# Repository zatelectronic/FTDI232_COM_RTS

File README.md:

<div align="center">

# FTDI232 COM RTS

**Conversor USB-Serial compacto com conector USB-C, chip FT232RL, seleção de tensão 3,3V / 5V, 3 LEDs de status e saída com pino RTS — totalmente SMD**

</div>

---

## 📋 Índice

- [FTDI232 COM RTS](#ftdi232-com-rts)
  - [📋 Índice](#-índice)
  - [Visão Geral](#visão-geral)
  - [Renders 3D](#renders-3d)
  - [Funcionalidades](#funcionalidades)
  - [Diagrama de Blocos](#diagrama-de-blocos)
  - [Especificações Técnicas](#especificações-técnicas)
  - [Lista de Materiais](#lista-de-materiais)
  - [Pinagem dos Conectores](#pinagem-dos-conectores)
    - [J2 — Saída Serial (6 pinos angulado)](#j2--saída-serial-6-pinos-angulado)
    - [JP1 — Seleção de Tensão](#jp1--seleção-de-tensão)
  - [Seleção de Tensão — JP1](#seleção-de-tensão--jp1)
  - [Aplicações](#aplicações)
  - [Estrutura do Repositório](#estrutura-do-repositório)
  - [Como Usar](#como-usar)
    - [Conexão com Arduino (programação)](#conexão-com-arduino-programação)
    - [Conexão com ESP8266 / ESP32](#conexão-com-esp8266--esp32)
    - [Instalação de drivers](#instalação-de-drivers)
  - [Sobre](#sobre)

---

## Visão Geral

**FTDI232 COM RTS** é um módulo conversor **USB para Serial (UART)** compacto e totalmente SMD, projetado pela **ZAT ELECTRONIC** utilizando **KiCad 10**. O módulo é baseado no chip **FT232RL** (SSOP-28), reconhecido automaticamente pelo sistema operacional sem necessidade de drivers adicionais na maioria das plataformas.

O diferencial deste módulo em relação a conversores convencionais é a presença do **pino RTS** no conector de saída de 6 pinos, além do tradicional conjunto **GND / VCC / TX / RX / DTR**. A tensão de saída é selecionável entre **3,3V e 5V** via jumper **(JP1)**, tornando o módulo compatível com uma ampla variedade de microcontroladores e módulos seriais. A entrada USB utiliza o conector **USB-C** (USB4105GFA SMD).

> 💡 Ideal para programação de Arduino bootloader, ESP8266, ESP32 sem USB nativo, módulos GSM, GPS e qualquer dispositivo com interface UART.

---

## Renders 3D

<div align="center">

*Vista superior — FT232RL SSOP-28, USB-C, LEDs SMD 0805, jumper JP1 e conector de 6 pinos (render da versão original)*

<br/>

*Vista isométrica — layout compacto SMD com saída de 6 pinos angulada*

</div>

---

## Funcionalidades

- ✅ **Chip FT232RL** (SSOP-28 SMD) — conversor USB-Serial com oscilador e EEPROM internos
- ✅ **Conector USB-C** (USB4105GFA) — USB 2.0, resistores de 5,1 kΩ no CC1/CC2 (R1, R2)
- ✅ **Seleção de tensão 5V / 3,3V** via jumper JP1 — define o pino VCC do J2 **e o VCCIO do FT232RL** (nível lógico das saídas)
- ✅ **Pino RTS** disponível no conector de saída
- ✅ **Pino DTR** disponível — reset automático de Arduino e bootloaders
- ✅ **3 LEDs SMD 0805** — D2 alimentação, D3 TX (CBUS0), D4 RX (CBUS1)
- ✅ **Diodo Schottky SS1P3L** (D1, DO-220AA SMD) — proteção contra corrente reversa entre VBUS e +5V
- ✅ **Capacitor de tântalo 10µF/16V** (C2, EIA-3216 SMD) + 100nF (C1) — filtragem da entrada VBUS
- ✅ **Desacoplamento do FT232RL** — 100nF no VCC (C3) e 1µF no 3V3OUT (C4), 0805 SMD
- ✅ **Resistores 1206 SMD** — R1/R2 5,1 kΩ (CC), R3 0 Ω (VBUS), R4–R6 1 kΩ (LEDs)
- ✅ **Saída por barra de 6 pinos 90°** (J2) na borda da placa

---

## Diagrama de Blocos

```
┌─────────────┐       ┌──────────────────┐       ┌─────────────────────────┐
│  USB-C  J1  │       │   FT232RL  U1    │       │  J2 (6 pinos 90°)       │
│ USB4105GFA  │──────►│   SSOP-28        │──────►│  1 DTR                  │
│  D+ / D-    │  USB  │  TXD/RXD/DTR/RTS │       │  2 RXD (entrada)        │
└──────┬──────┘       │  CBUS0 / CBUS1   │       │  3 TXD (saída)          │
       │ VBUS         │  VCCIO ◄── VOUT  │       │  4 VCC = VOUT           │
   R3 0Ω → D1 SS1P3L  └──────────────────┘       │  5 RTS                  │
       → +5V (VCC)            │ 3V3OUT           │  6 GND                  │
                          [JP1] 1-2 = 5V  /  2-3 = 3,3V → VOUT
                                                 └─────────────────────────┘
   D2 PWR (+5V)    D3 TX (CBUS0)    D4 RX (CBUS1)
```

---

## Especificações Técnicas

| Parâmetro | Valor |
|-----------|-------|
| **Chip conversor** | FT232RL (SSOP-28 SMD) |
| **Conector USB** | USB-C — USB4105GFA (USB 2.0) |
| **Tensão de saída / nível lógico** | 5V ou 3,3V (JP1 → VOUT = VCC do J2 e VCCIO do FT232RL) |
| **Saída 3,3V** | regulador interno do FT232RL (3V3OUT) — até ~50 mA |
| **Pinos do J2** | DTR, RXD, TXD, VCC, RTS, GND |
| **LEDs de status** | 3x SMD 0805 — D2 PWR, D3 TX, D4 RX |
| **Diodo de proteção** | SS1P3L — Schottky (DO-220AA SMD) |
| **Capacitor de entrada** | 10µF / 16V tântalo (EIA-3216) + 100nF |
| **Capacitores do FT232RL** | 100nF (VCC) e 1µF (3V3OUT), 0805 SMD |
| **Resistores** | 0Ω, 1kΩ, 5,1kΩ (1206 SMD) |
| **Jumper de tensão** | JP1 — 3 pinos 2,54mm (header vertical) |
| **Conector de saída** | J2 — 6 pinos 90° 2,54mm na borda |
| **Placa** | 41,7 × 18,4 mm, 2 camadas |
| **Ferramenta de Projeto** | KiCad 10 |

---

## Lista de Materiais

| Ref | Componente | Valor / Parte | Encapsulamento |
|-----|-----------|--------------|----------------|
| U1 | Conversor USB-Serial | FT232RL | SSOP-28 SMD |
| J1 | Conector USB | USB-C (USB4105GFA) | SMD + furos de fixação |
| J2 | Conector de Saída | 6 pinos — DTR/RXD/TXD/VCC/RTS/GND | Barra 90° 2,54mm |
| JP1 | Jumper de Tensão | 5V / VOUT / 3,3V | Header 3 pinos 2,54mm |
| D1 | Diodo Schottky | SS1P3L | DO-220AA (SMP) |
| D2 | LED PWR | LED 0805 | 0805 |
| D3 | LED TX | LED 0805 | 0805 |
| D4 | LED RX | LED 0805 | 0805 |
| C1 | Capacitor cerâmico (VBUS) | 100nF | 0805 SMD |
| C2 | Capacitor de tântalo (VBUS) | 10µF / 16V | EIA-3216-18 (A) |
| C3 | Capacitor cerâmico (VCC do FT232RL) | 100nF | 0805 SMD |
| C4 | Capacitor cerâmico (3V3OUT) | 1µF / 50V | 0805 SMD |
| R1, R2 | Resistor CC1 / CC2 (USB-C) | 5,1kΩ | 1206 SMD |
| R3 | Resistor jumper (VBUS) | 0Ω | 1206 SMD |
| R4 | Resistor do LED PWR | 1kΩ | 1206 SMD |
| R5, R6 | Resistor dos LEDs TX / RX | 1kΩ | 1206 SMD |

---

## Pinagem dos Conectores

### J2 — Saída Serial (6 pinos 90°)

| Pino | Sinal | Descrição |
|------|-------|-----------|
| 1 | DTR | Data Terminal Ready — reset automático Arduino |
| 2 | RXD | Recepção serial (entrada do FT232RL → ligar no TX do micro) |
| 3 | TXD | Transmissão serial (saída do FT232RL → ligar no RX do micro) |
| 4 | VCC | Tensão de saída (5V ou 3,3V conforme JP1) |
| 5 | RTS | Request To Send — saída do FT232RL (reset / controle de fluxo) |
| 6 | GND | Terra |

### JP1 — Seleção de Tensão

| Posição | VCC (J2.4) e VCCIO |
|---------|-----------|
| Pinos 1-2 | 5V |
| Pinos 2-3 | 3,3V |

---

## Seleção de Tensão — JP1

O jumper **JP1** liga o **VOUT** ao +5V (pinos 1-2) ou ao 3V3OUT do FT232RL (pinos 2-3). O VOUT alimenta o pino **VCC** do J2 e o **VCCIO** do FT232RL, que define o nível lógico de TXD, RXD, DTR, RTS e dos LEDs.

```
JP1 (pino 1 = +5V, 2 = VOUT, 3 = 3V3OUT):
  ●──●  ○    →  VOUT = 5V    (Arduino Uno, módulos 5V)
  ○  ●──●    →  VOUT = 3,3V  (ESP8266, ESP32, módulos 3,3V)
```

> ⚠️ Certifique-se de selecionar a tensão correta antes de conectar o dispositivo. Tensão incorreta pode danificar o hardware conectado.

> ℹ️ Sem o jumper o VCCIO fica sem alimentação e as saídas do FT232RL não funcionam: deixe sempre uma das duas posições fechada.

> ℹ️ Em 3,3V o regulador interno do FT232RL fornece no máximo ~50 mA no pino VCC.

---

## Aplicações

- 🤖 **Programação de Arduino** — upload de sketches via bootloader com auto-reset pelo DTR
- 📡 **Comunicação com ESP8266 / ESP32** — programação e monitor serial com lógica 3,3V
- 🛰️ **Módulos GPS e GSM** — interface serial para módulos com UART
- 🔧 **Debug serial** — monitoramento de comunicação UART em qualquer dispositivo
- 🏭 **Automação industrial** — interface USB-Serial para equipamentos com RS-232 (com adaptador)
- 💻 **Desenvolvimento embarcado** — substituto compacto de interfaces FTDI comerciais

---

## Estrutura do Repositório

```
FTDI232_COM_RTS/
├── FTDI232_COM_RTS.kicad_pro     # Projeto KiCad 10
├── FTDI232_COM_RTS.kicad_sch     # Esquemático: capa A2 (índice das folhas)
├── USB_POWER.kicad_sch           # Folha 02: USB-C + alimentação
├── FT232RL.kicad_sch             # Folha 03: FT232RL, LEDs TX/RX, jumper VCCIO
├── CONN.kicad_sch                # Folha 04: J2 + PWR_FLAG
├── FTDI232_COM_RTS.kicad_pcb     # Layout da PCB (KiCad 10)
├── FTDI232_COM_RTS.kicad_prl     # Configurações locais
├── FTDI232_COM_RTS.kicad_dru     # Regra: furo-cobre 0,15 mm só dentro do USB-C (J1)
├── Zat_TitleBlock.kicad_wks      # Title block ZAT ELECTRONIC
├── packages3D/                   # Modelos 3D arquivados (referência)
├── imagem_1.png                  # Render 3D superior
├── imagem_2.png                  # Render 3D isométrico
├── LEIA-ME_REVISAO_R01.md        # O que mudou na revisão R01
└── README.md
```

---

## Como Usar

### Conexão com Arduino (programação)

```
FTDI232 J2          Arduino Uno (header ICSP / Serial)
──────────────      ──────────────────────────────────
GND        ──────►  GND
VCC (5V)   ──────►  5V  (ou VIN)
TX         ──────►  RX  (pino 0)
RX         ──────►  TX  (pino 1)
DTR        ──────►  RESET (via capacitor 100nF)
```

### Conexão com ESP8266 / ESP32

```
FTDI232 J2          ESP8266 / ESP32
──────────────      ─────────────────
GND        ──────►  GND
VCC (3,3V) ──────►  3V3
TX         ──────►  RX
RX         ──────►  TX
RTS/DTR    ──────►  EN / GPIO0 (via circuito de 2 transistores da placa ESP)
```

### Instalação de drivers

O **FT232RL** é reconhecido nativamente pela maioria dos sistemas operacionais modernos. Caso necessário, os drivers oficiais estão disponíveis no site do fabricante do chip.

| Sistema Operacional | Driver |
|--------------------|--------|
| Windows 10 / 11 | Automático (Windows Update) ou driver VCP |
| Linux | Nativo (módulo `ftdi_sio`) |
| macOS | Nativo a partir do macOS 10.9+ |

---

## Sobre

<div align="center">

Projetado por **ZAT ELECTRONIC**

*FTDI232 COM RTS — Made in Brazil 🇧🇷*

</div>

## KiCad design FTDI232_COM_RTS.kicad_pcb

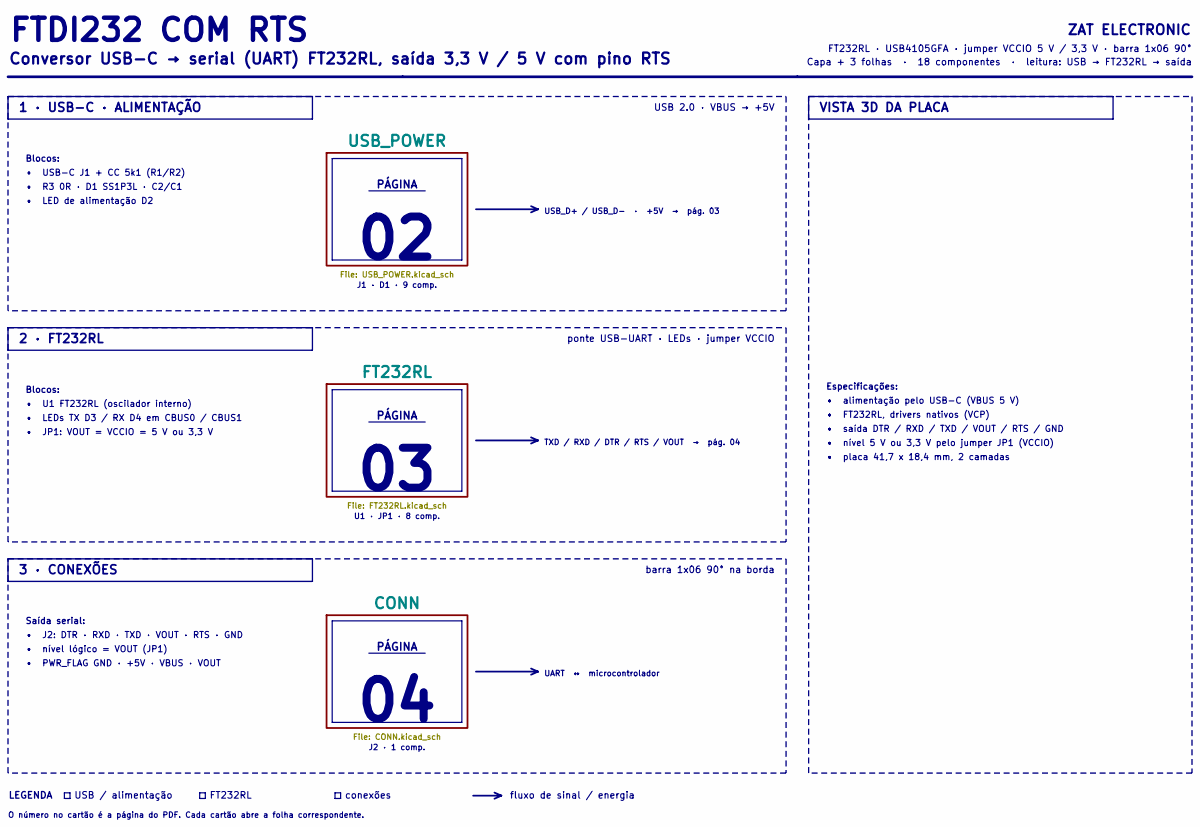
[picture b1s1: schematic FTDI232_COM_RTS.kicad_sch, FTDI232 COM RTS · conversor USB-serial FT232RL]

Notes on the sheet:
FTDI232 COM RTS
Conversor USB-C → serial (UART) FT232RL, saída 3,3 V / 5 V com pino RTS
ZAT ELECTRONIC
FT232RL · USB4105GFA · jumper VCCIO 5 V / 3,3 V · barra 1x06 90°
Capa + 3 folhas · 18 componentes · leitura: USB → FT232RL → saída
1 · USB-C · ALIMENTAÇÃO
USB 2.0 · VBUS → +5V
Blocos:
• USB-C J1 + CC 5k1 (R1/R2)
• R3 0R · D1 SS1P3L · C2/C1
• LED de alimentação D2
PÁGINA
J1 · D1 · 9 comp.
USB_D+ / USB_D- · +5V → pág. 03
2 · FT232RL
ponte USB-UART · LEDs · jumper VCCIO
• U1 FT232RL (oscilador interno)
• LEDs TX D3 / RX D4 em CBUS0 / CBUS1
• JP1: VOUT = VCCIO = 5 V ou 3,3 V
U1 · JP1 · 8 comp.
TXD / RXD / DTR / RTS / VOUT → pág. 04
3 · CONEXÕES
barra 1x06 90° na borda
Saída serial:
• J2: DTR · RXD · TXD · VOUT · RTS · GND
• nível lógico = VOUT (JP1)
• PWR_FLAG GND · +5V · VBUS · VOUT
J2 · 1 comp.
UART ↔ microcontrolador
VISTA 3D DA PLACA
Especificações:
• alimentação pelo USB-C (VBUS 5 V)
• FT232RL, drivers nativos (VCP)
• saída DTR / RXD / TXD / VOUT / RTS / GND
• nível 5 V ou 3,3 V pelo jumper JP1 (VCCIO)
• placa 41,7 x 18,4 mm, 2 camadas
LEGENDA
USB / alimentação
FT232RL
conexões

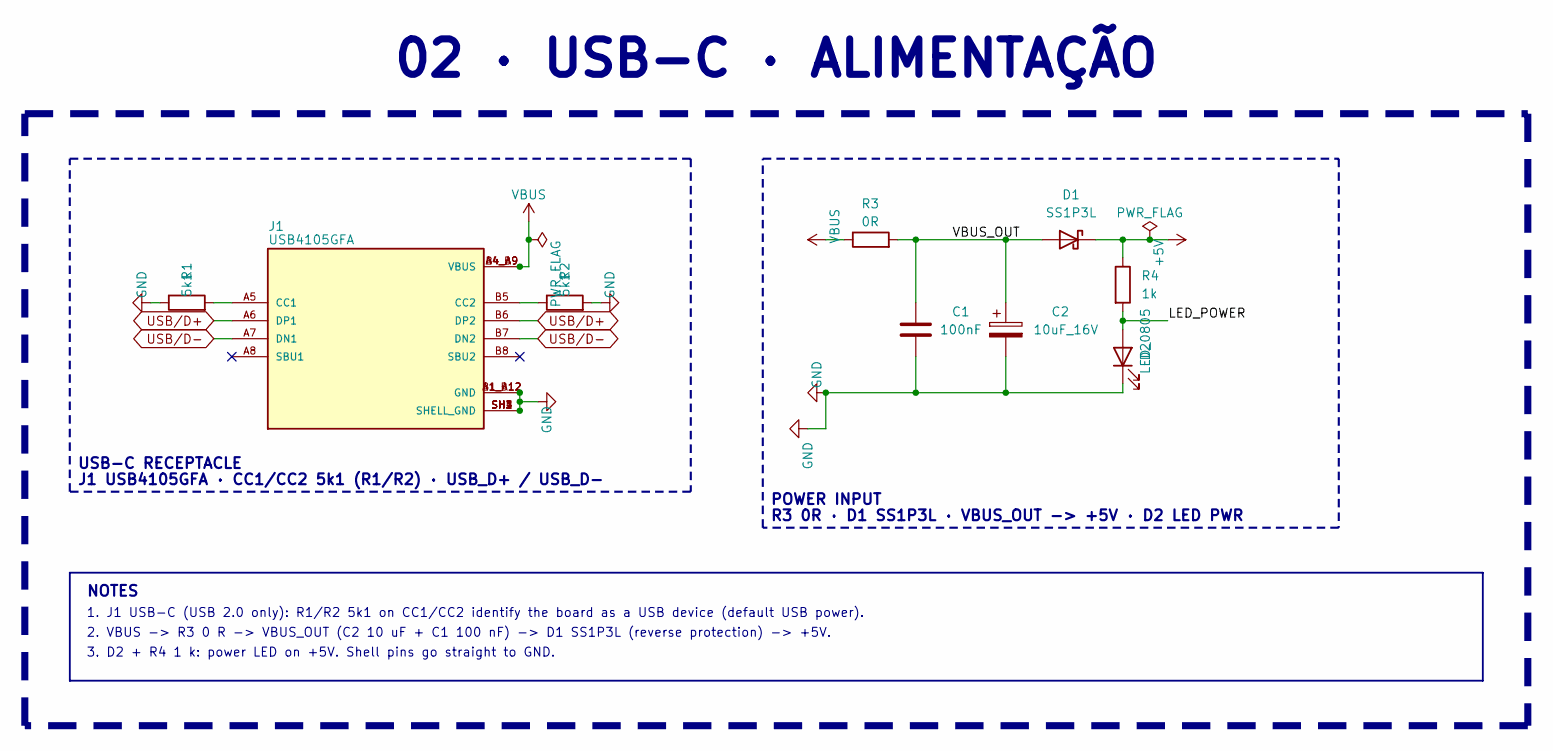
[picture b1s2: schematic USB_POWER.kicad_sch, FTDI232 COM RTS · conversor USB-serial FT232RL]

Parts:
C1: 100nF; C_0805_2012Metric
C2: 10uF_16V; CP_EIA-3216-18_Kemet-A
D1: SS1P3L; D_SMP_DO-220AA
D2: LED_0805; LED_0805_2012Metric
J1: USB4105GFA; PARTREV B3
R1, R2: 5k1; R_1206_3216Metric
R3: 0R; R_1206_3216Metric
R4: 1k; R_1206_3216Metric

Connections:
+5V: D1.1 (K), R4.1; also elsewhere on the board
/USB_POWER/LED_POWER: D2.2 (A), R4.2
/USB_POWER/VBUS_OUT: C1.1, C2.1, D1.2 (A), R3.2
GND: C1.2, C2.2, D2.1 (K), J1.A1_B12 (GND), J1.B1_A12 (GND), J1.SH1 (SHELL_GND), J1.SH2 (SHELL_GND), J1.SH3 (SHELL_GND), J1.SH4 (SHELL_GND), R1.1, R2.2; also elsewhere on the board
unnamed: J1.A5 (CC1), R1.2
unnamed: J1.B5 (CC2), R2.1
USB/D+: J1.A6 (DP1), J1.B6 (DP2); also elsewhere on the board
USB/D-: J1.A7 (DN1), J1.B7 (DN2); also elsewhere on the board
VBUS: J1.A4_B9 (VBUS), J1.B4_A9 (VBUS), R3.1

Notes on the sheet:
USB-C RECEPTACLE
J1 USB4105GFA · CC1/CC2 5k1 (R1/R2) · USB_D+ / USB_D-
POWER INPUT
R3 0R · D1 SS1P3L · VBUS_OUT -> +5V · D2 LED PWR
NOTES
1. J1 USB-C (USB 2.0 only): R1/R2 5k1 on CC1/CC2 identify the board as a USB device (default USB power).
2. VBUS -> R3 0 R -> VBUS_OUT (C2 10 uF + C1 100 nF) -> D1 SS1P3L (reverse protection) -> +5V.
3. D2 + R4 1 k: power LED on +5V. Shell pins go straight to GND.
02 · USB-C · ALIMENTAÇÃO

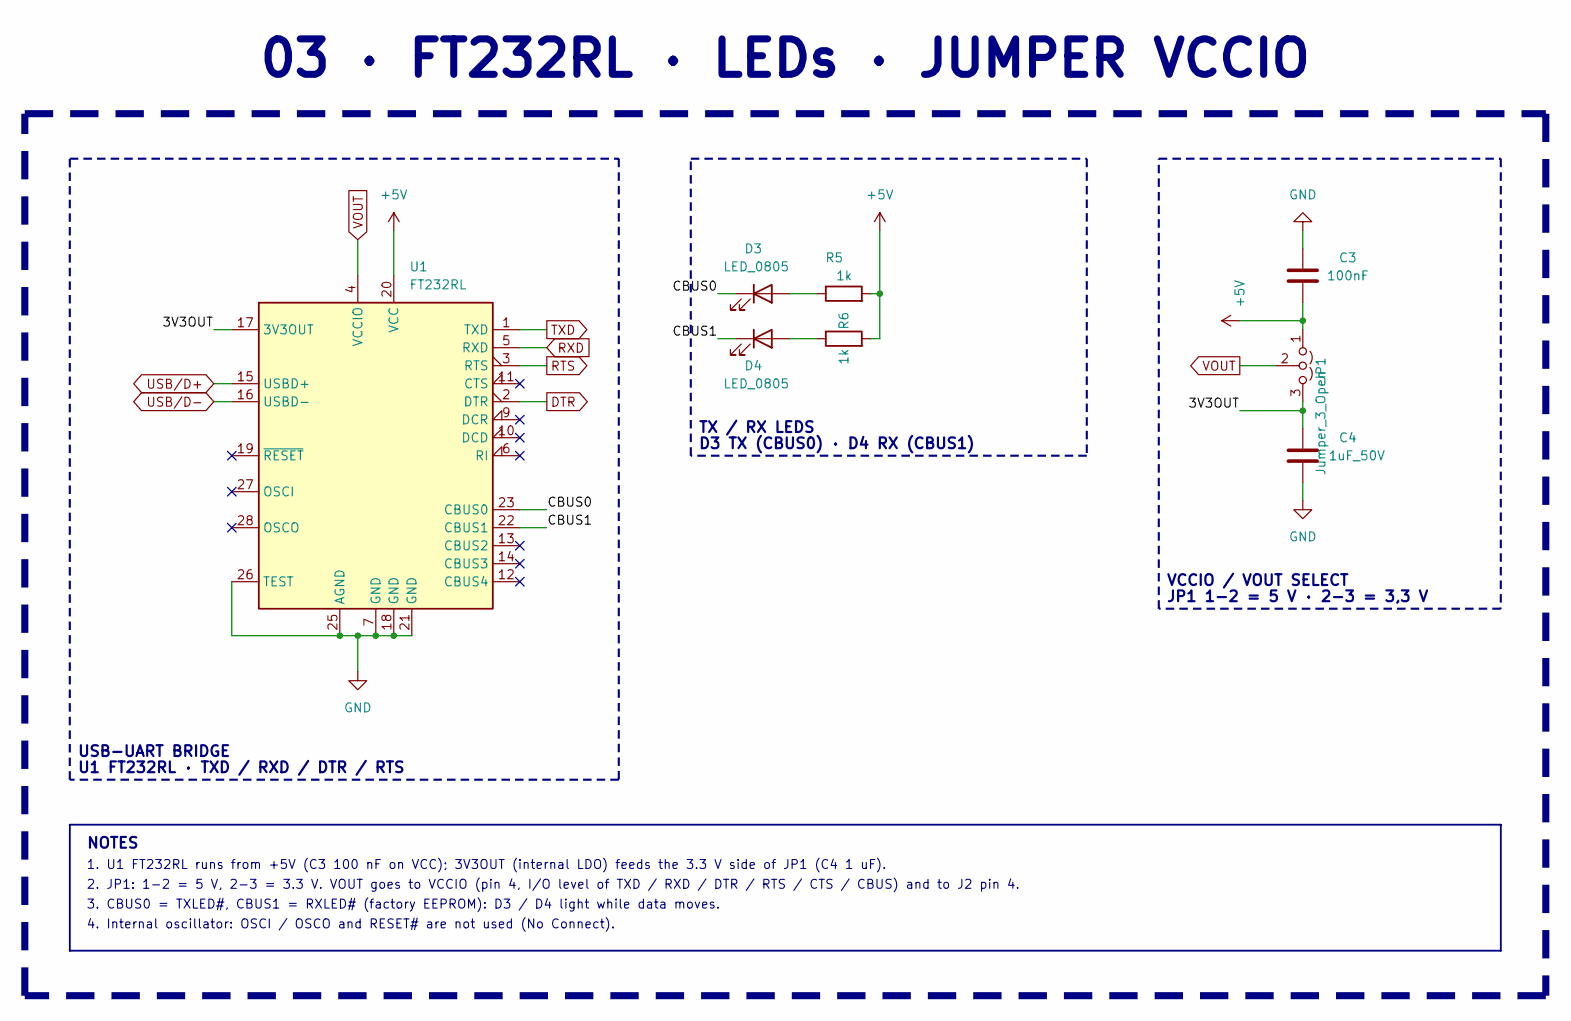
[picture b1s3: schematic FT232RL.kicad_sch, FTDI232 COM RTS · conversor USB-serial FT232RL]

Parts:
C3: 100nF; C_0805_2012Metric
C4: 1uF_50V; C_0805_2012Metric
D3, D4: LED_0805; LED_0805_2012Metric
JP1: Jumper_3_Open; PinHeader_1x03_P2.54mm_Vertical
R5, R6: 1k; R_1206_3216Metric
U1: FT232RL; SSOP-28_5.3x10.2mm_P0.65mm

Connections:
+5V: C3.1, JP1.1 (A), R5.2, R6.2, U1.20 (VCC); also elsewhere on the board
/FT232RL/3V3OUT: C4.2, JP1.3 (B), U1.17 (3V3OUT)
/FT232RL/CBUS0: D3.1 (K), U1.23 (CBUS0)
/FT232RL/CBUS1: D4.1 (K), U1.22 (CBUS1)
DTR: U1.2 (DTR); also elsewhere on the board
GND: C3.2, C4.1, U1.7 (GND), U1.18 (GND), U1.21 (GND), U1.25 (AGND), U1.26 (TEST); also elsewhere on the board
unnamed: D3.2 (A), R5.1
unnamed: D4.2 (A), R6.1
RTS: U1.3 (RTS); also elsewhere on the board
RXD: U1.5 (RXD); also elsewhere on the board
TXD: U1.1 (TXD); also elsewhere on the board
USB/D+: U1.15 (USBD+); also elsewhere on the board
USB/D-: U1.16 (USBD-); also elsewhere on the board
VOUT: JP1.2 (C), U1.4 (VCCIO); also elsewhere on the board

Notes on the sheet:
USB-UART BRIDGE
U1 FT232RL · TXD / RXD / DTR / RTS
TX / RX LEDS
D3 TX (CBUS0) · D4 RX (CBUS1)
VCCIO / VOUT SELECT
JP1 1-2 = 5 V · 2-3 = 3,3 V
NOTES
1. U1 FT232RL runs from +5V (C3 100 nF on VCC); 3V3OUT (internal LDO) feeds the 3.3 V side of JP1 (C4 1 uF).
2. JP1: 1-2 = 5 V, 2-3 = 3.3 V. VOUT goes to VCCIO (pin 4, I/O level of TXD / RXD / DTR / RTS / CTS / CBUS) and to J2 pin 4.
3. CBUS0 = TXLED#, CBUS1 = RXLED# (factory EEPROM): D3 / D4 light while data moves.
4. Internal oscillator: OSCI / OSCO and RESET# are not used (No Connect).
03 · FT232RL · LEDs · JUMPER VCCIO

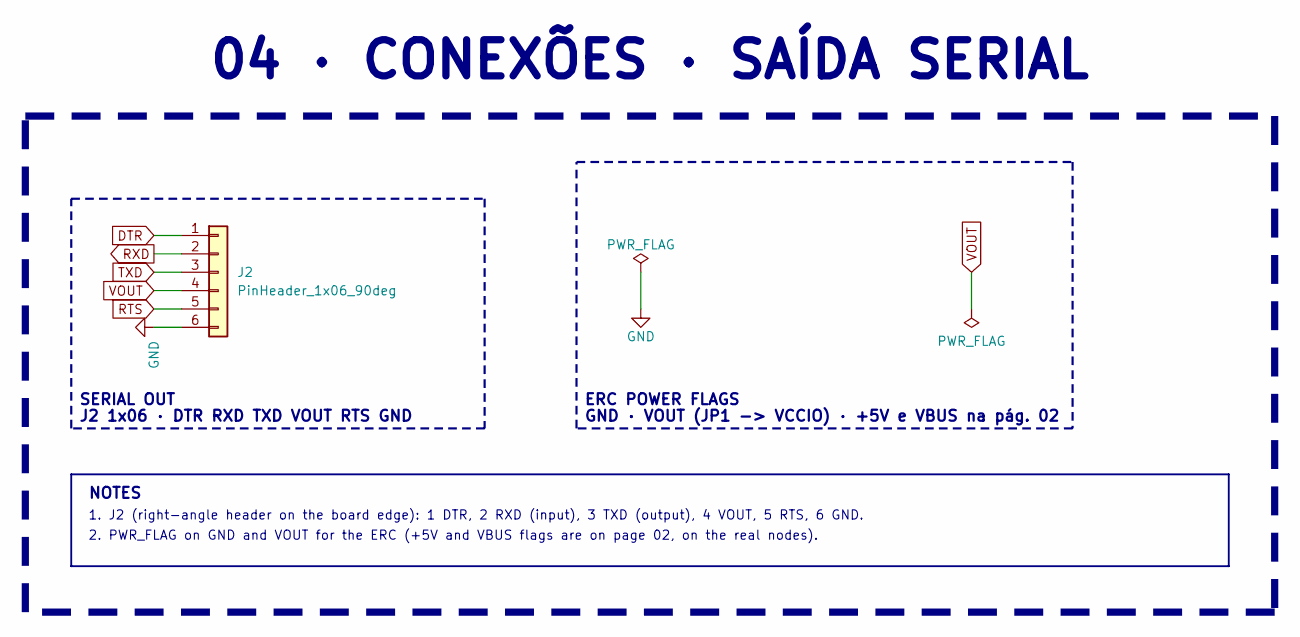
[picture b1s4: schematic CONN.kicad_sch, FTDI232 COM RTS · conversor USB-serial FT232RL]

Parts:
J2: PinHeader_1x06_90deg; PinHeader_1x06_P2.54mm_RightAngle_EdgeMount

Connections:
DTR: J2.1; also elsewhere on the board
GND: J2.6; also elsewhere on the board
RTS: J2.5; also elsewhere on the board
RXD: J2.2; also elsewhere on the board
TXD: J2.3; also elsewhere on the board
VOUT: J2.4; also elsewhere on the board

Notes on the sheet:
SERIAL OUT
J2 1x06 · DTR RXD TXD VOUT RTS GND
ERC POWER FLAGS
GND · VOUT (JP1 -> VCCIO) · +5V e VBUS na pág. 02
NOTES
1. J2 (right-angle header on the board edge): 1 DTR, 2 RXD (input), 3 TXD (output), 4 VOUT, 5 RTS, 6 GND.
2. PWR_FLAG on GND and VOUT for the ERC (+5V and VBUS flags are on page 02, on the real nodes).
04 · CONEXÕES · SAÍDA SERIAL

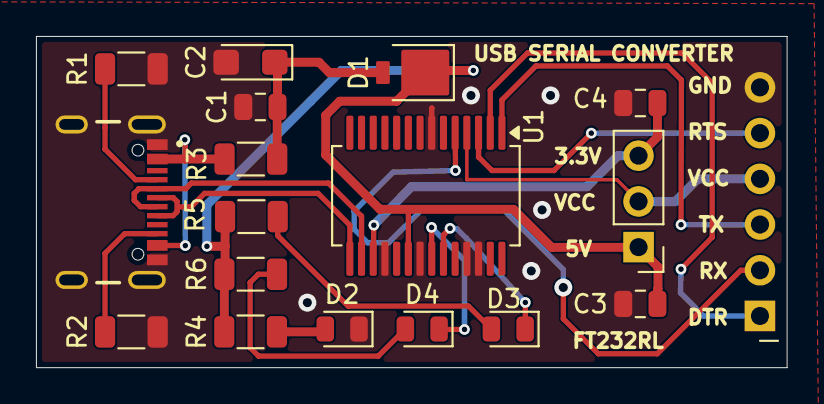
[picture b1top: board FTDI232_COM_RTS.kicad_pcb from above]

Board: 2 copper layers, 41.7 x 18.4 mm, 18 parts (0 on the bottom side), 19 nets.

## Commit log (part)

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2026-06-28 commit_3
2026-06-29 COMMIT-4
